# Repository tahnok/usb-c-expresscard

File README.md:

# usb-c-expresscard

An expresscard that breaks out the USB 2.0 pins to a USB-C port.
Also boosts 3.3V to 5V, and adds a chip to deal with USB-C power switching.

More detailed design notes on https://notes.tahnok.ca

# R1

Status: pending

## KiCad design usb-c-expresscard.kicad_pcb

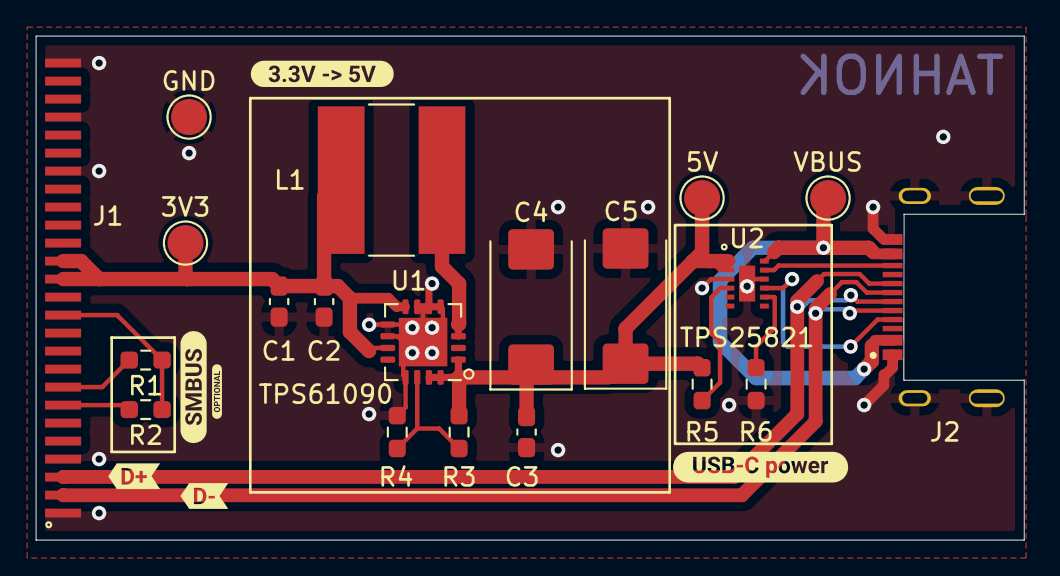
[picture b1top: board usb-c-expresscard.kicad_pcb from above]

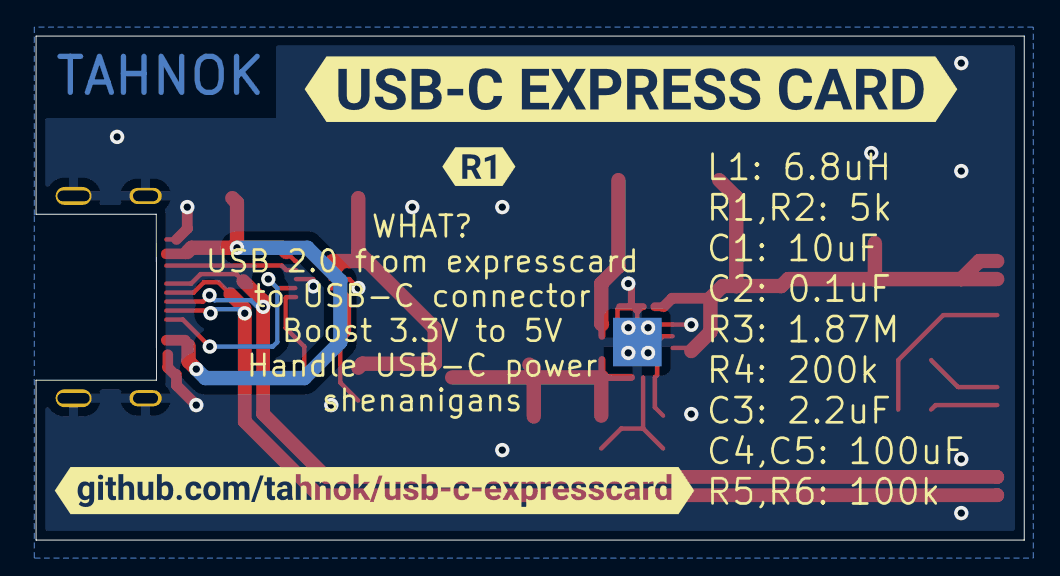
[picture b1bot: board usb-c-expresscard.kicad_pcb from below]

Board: 2 copper layers, 54.9 x 28.0 mm, 29 parts (3 on the bottom side), 15 nets.

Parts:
3V3, 5V: TestPoint; TestPoint_Pad_D2.0mm
C1: 10uF; C_0603_1608Metric_Pad1.08x0.95mm_HandSolder
C2: 0.1uF; C_0603_1608Metric_Pad1.08x0.95mm_HandSolder
C3: 2.2uF; C_0603_1608Metric_Pad1.08x0.95mm_HandSolder
C4, C5: 100uF; CP_EIA-7343-20_Kemet-V_Pad2.25x2.55mm_HandSolder
GND: TestPoint; TestPoint_Pad_D2.0mm
J1: ExpressCard; ExpressCard_easyeda
J2: USB_C_Receptacle_USB2.0; MOLEX_2169900003_usb_c
L1: 6.8uH @ 2A; L_Bourns-SRN8040_8x8.15mm
R1, R2: 5k; R_0603_1608Metric_Pad0.98x0.95mm_HandSolder
R3: 1.87M; R_0603_1608Metric_Pad0.98x0.95mm_HandSolder
R4: 200K; R_0603_1608Metric_Pad0.98x0.95mm_HandSolder
R5, R6: 100k; R_0603_1608Metric_Pad0.98x0.95mm_HandSolder
U1: TPS61090; Texas_S-PVQFN-N16_EP2.7x2.7mm_ThermalVias
U2: TPS25821; TPS25821DSSR
VBUS: TestPoint; TestPoint_Pad_D2.0mm
kibuzzard-65DE8A1F: G***; kibuzzard-65DE8A1F
kibuzzard-65DE8A3E: G***; kibuzzard-65DE8A3E
kibuzzard-65DE8B98: G***; kibuzzard-65DE8B98
kibuzzard-65DE8C34: G***; kibuzzard-65DE8C34
kibuzzard-65DE8EC7: G***; kibuzzard-65DE8EC7
kibuzzard-65DE8EF4: G***; kibuzzard-65DE8EF4
kibuzzard-65DE8F1B: G***; kibuzzard-65DE8F1B
kibuzzard-65DE8FDD: G***; kibuzzard-65DE8FDD
kibuzzard-65DE897E: G***; kibuzzard-65DE897E

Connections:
+3.3V: 3V3.1, C1.1, C2.1, J1.14 (3V3), J1.15 (3V3), L1.2, U1.8 (VBAT), U1.11 (EN)
+5V: 5V.1, C3.1, C4.1, C5.1, R3.1, R5.1, U1.1 (VOUT), U1.15 (VOUT), U1.16 (VOUT), U2.1 (IN), U2.2 (IN)
/D+: J1.3 (USBD+), J2.A6 (D+), J2.B6 (D+)
/D-: J1.2 (USBD-), J2.A7 (D-), J2.B7 (D-)
/VBUS: J2.A4_B9 (VBUS), J2.B4_A9 (VBUS), U2.12 (OUT), VBUS.1
GND: C1.2, C2.2, C3.2, C4.2, C5.2, GND.1, J1.1 (GND), J1.4 (~CPUSB), J1.20 (GND), J1.23 (GND), J1.26 (GND), J2.A1_B12 (GND), J2.B1_A12 (GND), J2.S1 (SHIELD), J2.S2, J2.S3, J2.S4, R4.2, R6.2, U1.5 (PGND), U1.6 (PGND), U1.7 (PGND), U1.9 (LBI), U1.10 (SYNC), U1.13 (GND), U1.17 (PAD), U2.3 (CHG), U2.10 (GND), U2.13 (Thermal_Pad)
unnamed: J1.7 (SMBCLK), R2.2
unnamed: J1.8 (SMDDATA), R1.2
unnamed: J1.12 (3V3_AUX), R1.1, R2.1
unnamed: J2.A5 (CC1), U2.9 (CC1)
unnamed: J2.B5 (CC2), U2.11 (CC2)
unnamed: L1.1, U1.3 (SW), U1.4 (SW)
unnamed: R3.2, R4.1, U1.14 (FB)
unnamed: R5.2, U2.4 (EN)
unnamed: R6.1, U2.8 (REF)

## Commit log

2024-02-23 v1 I guess
2024-02-28 r1 but with less old stuff
